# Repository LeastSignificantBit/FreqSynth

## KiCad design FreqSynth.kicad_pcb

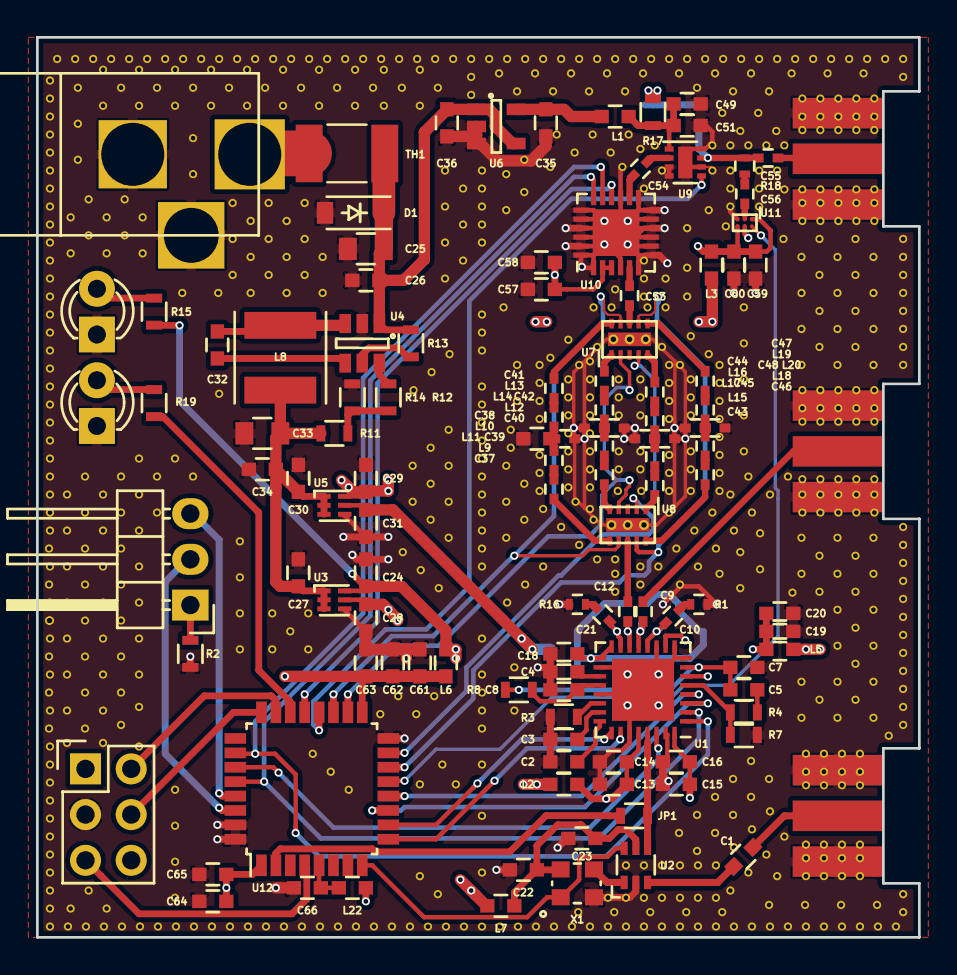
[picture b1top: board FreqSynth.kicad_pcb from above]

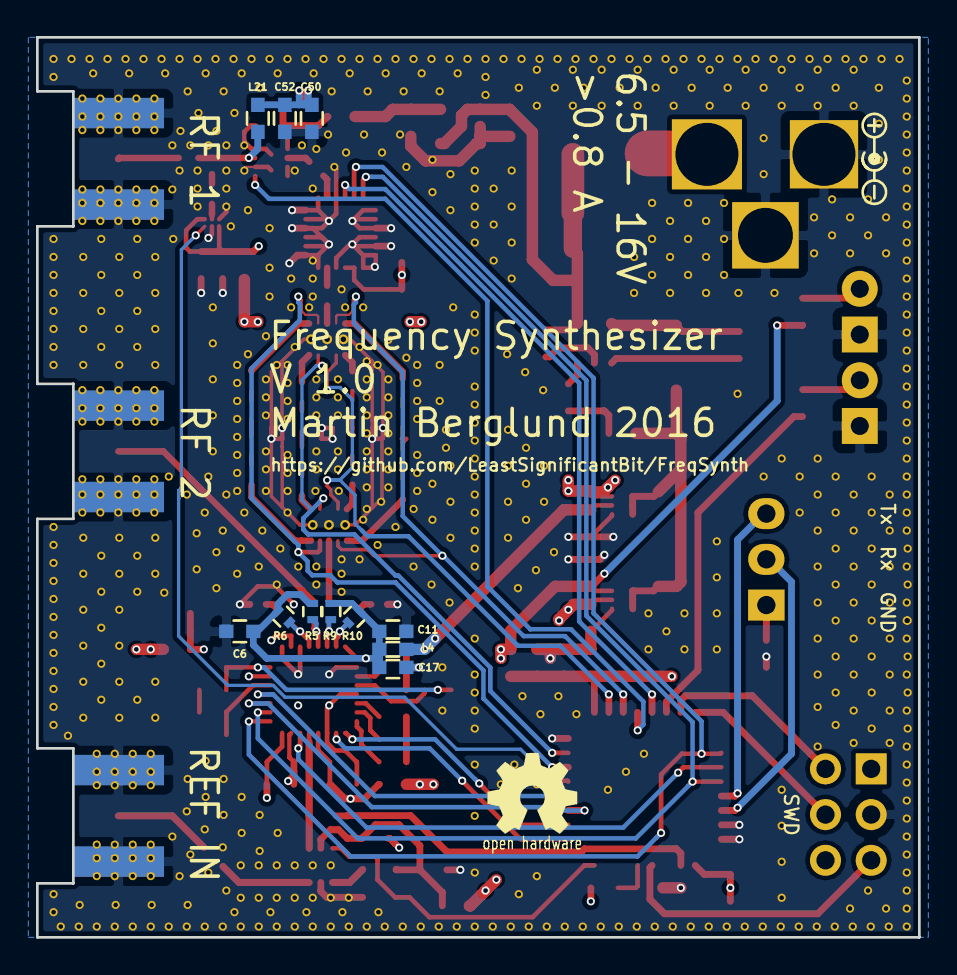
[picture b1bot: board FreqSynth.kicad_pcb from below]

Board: 4 copper layers, 49.0 x 50.0 mm, 131 parts (11 on the bottom side), 96 nets.

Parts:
C1, C6, C11, C13, C15, C17, C19, C22, C50, C57, C59, C62, C64, C66: 10nF; C_0603
C2, C3, C4: 1uF; C_0603
C5, C36, C51: 100nF; C_0603
C7: 12nF; C_0603
C8: 820pF; C_0603
C9, C10, C12, C21, C53, C54, C55, C56: 1nF_RF; C_0402
C14, C16, C18, C20, C23, C58, C60, C63, C65: 100pF; C_0603
C24, C26, C27, C28, C29, C30, C31, C32, C34, C35, C49, C61: 1µF; C_0603
C25, C33: 22µF 16V; C_0805
C37, C38: 100pF_RF; C_0402
C39: 6pF_RF; C_0402
C40, C41: 0.5pF_RF; C_0402
C42: 2pF_RF; C_0402
C43, C44: 0.8pF_RF; C_0402
C45: 4pF_RF; C_0402
C46, C47: 2.4pF_RF; C_0402
C48: 5pF_RF; C_0402
C52: 10pF; C_0603
D1: CPL-DIO-MBR0520; SOD-123
D2: GREEN; LED-3MM
D3: YELLOW; LED-3MM
JP1: Jumper_NC_Small; R_0603
L1, L2, L3, L4, L5, L6, L7, L22: Ferrite; L_0603
L8: 6.8µH 2.5A; NRS5030T6R8MMGJ
L9, L10: 8nH; L_0402
L11: 200nH; L_0603
L12, L13: 2.5nH; L_0402
L14: 0.6nH; L_0402
L15, L16: 5nH; L_0402
L17: 1nH; L_0402
L18, L19: 6.1nH; L_0402
L20: 3nH; L_0402
L21: 100nH; L_0603
P1: CPL-CON-BARREL-2.1MM; BARREL_JACK
P2: RF1; SMA_edge
P3: RF2; SMA_edge
P4: CONN_01X03; Pin_Header_Angled_1x03
P5: REF_IN; SMA_edge
P6: SWD; Pin_Header_Straight_2x03
R1, R5, R6, R9, R10, R16: 49.9R; R_0402
R2: 0R; R_0603
R3: 5.1k; R_0603
R4: 30.1R; R_0603
R7: 90.9R; R_0603
R8: 240R; R_0603
R11: 45.3k; R_0603
R12: 59k; R_0603
R13: 100k; R_0603
R14: 11.3k; R_0603
R15, R19: 180R; R_0603
R17: 1.8R; R_0603
R18: 100R; R_0402
TH1: 750mA working 1.5A trip; SMD_THERMISTOR
U1: MAX2870; QFN-32-1EP_5x5mm_Pitch0.5mm
U2: TS5A3159; SC-70-6
U3, U5: TLV7113333DDSET; WSON-6
U4: AP65101; SOT-23-6
U6: RT9069-50GB; SOT-23-5
U7, U8: SKY13322-375LF; MLPD-10
U9: TRF37A75; DFN-8-1EP_2x2mm_Pitch0.5mm
U10: PE43711; QFN-24-1EP_4x4mm_Pitch0.5mm
U11: LMH2110; WFBGA-6
U12: STM32F030K6T6; LQFP-32_7x7mm_Pitch0.8mm
X1: 25MHz ±5ppm 3.3V 33mA; OSC_2.7x2.4mm

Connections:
/3v3: C29.2, L3.1, L7.1, U5.6
/5V5: C35.1, L1.1, U6.5
/Amplifier/3V3: C57.1, C58.1, C59.1, C60.1, L3.2, U10.2, U10.3, U11.A1, U11.C2
/Amplifier/ATTEN_CS: U10.16, U12.21
/Amplifier/PWDN: U9.5, U12.20
/Amplifier/RF_IN: C53.2, U7.8
/Amplifier/RF_OUT: C55.1, P2.1
/Amplifier/VCC_AMP: C49.2, C51.2, L1.2, R17.1, U9.1
/Clock/3V3: C22.1, C23.1, L7.2, U2.5, X1.4
/Clock/EXT_REF: C1.1, U2.3
/FILT1: U7.9, U8.7, U12.19
/FILT2: U7.7, U8.9, U12.14
/FILT3: U7.4, U8.2, U12.15
/FILT4: U7.2, U8.4, U12.18
/MCU/ADC1: U11.A2, U12.13
/MCU/CE_PLL: U1.4, U12.12
/MCU/CLK_IN: JP1.2, U12.2
/MCU/CS_PLL: U1.3, U12.11
/MCU/EN_PLL: U1.26, U12.9
/MCU/INT_CLK_EN: U2.6, U12.8, X1.1
/MCU/LD_PLL: U1.25, U12.10
/MCU/RX: P4.2, U12.30
/MCU/TX: P4.3, U12.29
/MCU/VCC_D: C61.1, C62.1, C63.1, C64.1, C65.1, L6.2, L22.1, P6.1, U12.1, U12.17
/MISO: U1.30, U12.27
/MOSI: U1.2, U10.18, U12.28
/PLL/CLK_REF: JP1.1, U1.29, U2.4
/PLL/RF+: C12.1, U8.8
/PLL/RF-: C21.1, R16.1
/PLL/RFA_N: C9.2, R5.2, U1.13
/PLL/RFA_P: C10.2, R6.2, U1.12
/PLL/RFB_N: C21.2, R10.2, U1.15
/PLL/RFB_P: C12.2, R9.2, U1.14
/PLL/RF_BALANCED+: C10.1, R1.1
/PLL/RF_BALANCED-: C9.1, P3.1
/PLL/TUNE: C8.2, R8.1, U1.20
/PLL/VCC_D: C13.1, C14.1, C15.1, C16.1, L2.2, U1.28, U1.32
/PLL/VCC_PLL: C19.1, C20.1, L5.2, U1.6, U1.10
/PLL/VCC_RF: C6.1, C11.1, C17.1, C18.1, L4.2, R5.1, R6.1, R9.1, R10.1, U1.16, U1.17
/Power/4V0: C27.1, C30.1, C33.1, C34.1, L8.2, R11.2, U3.1, U3.2, U3.3, U5.1, U5.2, U5.3
/Power/VCC_D: C24.2, L2.1, L6.1, R15.1, U3.6
/Power/VCC_PLL: C28.1, L5.1, U3.5
/Power/VCC_RF: C31.1, L4.1, U5.5
/Power/VIN: C25.1, C26.1, C36.1, D1.1, R13.1, TH1.1, U4.1, U6.1, U6.4
/SCK: U1.1, U10.17, U12.26
Earth: C2.1, C3.1, C4.1, C6.2, C7.1, C8.1, C11.2, C13.2, C14.2, C15.2, C16.2, C17.2, C18.2, C19.2, C20.2, C22.2, C23.2, C24.1, C25.2, C26.2, C27.2, C28.2, C29.1, C30.2, C31.2, C33.2, C34.2, C35.2, C36.2, C39.2, C42.2, C45.2, C48.2, C49.1, C50.2, C51.1, C52.1, C57.2, C58.2, C59.2, C60.2, C61.2, C62.2, C63.2, C64.2, C65.2, C66.2, D1.2, D2.1, D3.1, L11.2, L14.2, L17.2, L20.2, P1.2, P1.3, P2.2, P3.2, P5.2, P6.3, R1.2, R2.2, R3.1, R7.1, R14.1, R16.2, U1.8, U1.9, U1.11, U1.18, U1.21, U1.27, U1.31, U1.33, U2.2, U3.4, U4.2, U5.4, U6.2, U6.3, U7.11, U8.11, U9.3, U9.4, U9.6, U9.8, U9.9, U10.1, U10.4, U10.6, U10.7, U10.8, U10.9, U10.10, U10.11, U10.12, U10.13, U10.15, U10.19, U10.20, U10.21, U10.22, U10.23, U10.24, U10.25, U11.B2, U11.C1, U12.16, U12.31, U12.32, X1.2
unnamed: C1.2, P5.1
unnamed: C2.2, U1.24
unnamed: C3.2, U1.23
unnamed: C4.2, U1.19
unnamed: C5.1, C7.2, R8.2, U1.7
unnamed: C5.2, R4.1
unnamed: C32.1, U4.4
unnamed: C32.2, L8.1, U4.3
unnamed: C37.1, U8.6
unnamed: C37.2, L9.2
unnamed: C38.1, L10.2
unnamed: C38.2, U7.10
unnamed: C39.1, L9.1, L10.1, L11.1
unnamed: C40.1, U8.5
unnamed: C40.2, L12.2
unnamed: C41.1, U7.1
unnamed: C41.2, L13.2
unnamed: C42.1, L12.1, L13.1, L14.1
unnamed: C43.1, U8.1
unnamed: C43.2, L15.2
unnamed: C44.1, U7.5
unnamed: C44.2, L16.2
unnamed: C45.1, L15.1, L16.1, L17.1
unnamed: C46.1, U8.10
unnamed: C46.2, L18.2
unnamed: C47.1, U7.6
unnamed: C47.2, L19.2
unnamed: C48.1, L18.1, L19.1, L20.1
unnamed: C50.1, C52.2, L21.1, R17.2
unnamed: C53.1, U10.5
unnamed: C54.1, U9.2
unnamed: C54.2, U10.14
unnamed: C55.2, L21.2, R18.1, U9.7
unnamed: C56.1, U11.B1
unnamed: C56.2, R18.2
unnamed: C66.1, L22.2, U12.5
unnamed: D2.2, R15.2
unnamed: D3.2, R19.2
unnamed: P1.1, TH1.2
unnamed: P4.1, R2.1
unnamed: P6.2, U12.23
unnamed: P6.4, U12.24
unnamed: P6.5, U12.4
unnamed: R3.2, U1.22
unnamed: R4.2, R7.2, U1.5
unnamed: R11.1, R12.1, R14.2
unnamed: R12.2, U4.6
unnamed: R13.2, U4.5
unnamed: R19.1, U12.22
unnamed: U2.1, X1.3

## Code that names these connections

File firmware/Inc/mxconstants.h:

/**
  ******************************************************************************
  * File Name          : mxconstants.h
  * Description        : This file contains the common defines of the application
  ******************************************************************************
  *
  * COPYRIGHT(c) 2016 STMicroelectronics
  *
  * Redistribution and use in source and binary forms, with or without modification,
  * are permitted provided that the following conditions are met:
  *   1. Redistributions of source code must retain the above copyright notice,
  *      this list of conditions and the following disclaimer.
  *   2. Redistributions in binary form must reproduce the above copyright notice,
  *      this list of conditions and the following disclaimer in the documentation
  *      and/or other materials provided with the distribution.
  *   3. Neither the name of STMicroelectronics nor the names of its contributors
  *      may be used to endorse or promote products derived from this software
  *      without specific prior written permission.
  *
  * THIS SOFTWARE IS PROVIDED BY THE COPYRIGHT HOLDERS AND CONTRIBUTORS "AS IS"
  * AND ANY EXPRESS OR IMPLIED WARRANTIES, INCLUDING, BUT NOT LIMITED TO, THE
  * IMPLIED WARRANTIES OF MERCHANTABILITY AND FITNESS FOR A PARTICULAR PURPOSE ARE
  * DISCLAIMED. IN NO EVENT SHALL THE COPYRIGHT HOLDER OR CONTRIBUTORS BE LIABLE
  * FOR ANY DIRECT, INDIRECT, INCIDENTAL, SPECIAL, EXEMPLARY, OR CONSEQUENTIAL
  * DAMAGES (INCLUDING, BUT NOT LIMITED TO, PROCUREMENT OF SUBSTITUTE GOODS OR
  * SERVICES; LOSS OF USE, DATA, OR PROFITS; OR BUSINESS INTERRUPTION) HOWEVER
  * CAUSED AND ON ANY THEORY OF LIABILITY, WHETHER IN CONTRACT, STRICT LIABILITY,
  * OR TORT (INCLUDING NEGLIGENCE OR OTHERWISE) ARISING IN ANY WAY OUT OF THE USE
  * OF THIS SOFTWARE, EVEN IF ADVISED OF THE POSSIBILITY OF SUCH DAMAGE.
  *
  ******************************************************************************
  */
/* Define to prevent recursive inclusion -------------------------------------*/
#ifndef __MXCONSTANT_H
#define __MXCONSTANT_H
  /* Includes ------------------------------------------------------------------*/

/* USER CODE BEGIN Includes */

/* USER CODE END Includes */

/* Private define ------------------------------------------------------------*/

#define INT_CLK_EN_Pin GPIO_PIN_2
#define INT_CLK_EN_GPIO_Port GPIOA
#define EN_PLL_Pin GPIO_PIN_3
#define EN_PLL_GPIO_Port GPIOA
#define LD_PLL_Pin GPIO_PIN_4
#define LD_PLL_GPIO_Port GPIOA
#define CS_PLL_Pin GPIO_PIN_5
#define CS_PLL_GPIO_Port GPIOA
#define CE_PLL_Pin GPIO_PIN_6
#define CE_PLL_GPIO_Port GPIOA
#define ADC_POWER_DET_Pin GPIO_PIN_7
#define ADC_POWER_DET_GPIO_Port GPIOA
#define FILT2_Pin GPIO_PIN_0
#define FILT2_GPIO_Port GPIOB
#define FILT3_Pin GPIO_PIN_1
#define FILT3_GPIO_Port GPIOB
#define FILT4_Pin GPIO_PIN_8
#define FILT4_GPIO_Port GPIOA
#define FILT1_Pin GPIO_PIN_9
#define FILT1_GPIO_Port GPIOA
#define PWDWN_Pin GPIO_PIN_10
#define PWDWN_GPIO_Port GPIOA
#define ATTEN_CS_Pin GPIO_PIN_11
#define ATTEN_CS_GPIO_Port GPIOA
#define RED_LED_Pin GPIO_PIN_12
#define RED_LED_GPIO_Port GPIOA
/* USER CODE BEGIN Private defines */

/* USER CODE END Private defines */

/**
  * @}
  */ 

/**
  * @}
*/ 

#endif /* __MXCONSTANT_H */
/************************ (C) COPYRIGHT STMicroelectronics *****END OF FILE****/

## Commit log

2016-08-29 init
2016-08-29 fixed broken stuff
2016-08-30 multiple additions
2016-08-30 Amplifier
2016-08-30 added amplifier
2016-08-31 Set the designrules to match 4 layer OSHpark DRC
2016-08-31 Fixed Amplifier, Added manf# field, ERC cleanup
2016-08-31 housekeeping
2016-08-31 attenuator
2016-09-01 Removed rescuelib
2016-09-01 Added some inductor values
2016-09-01 small edit
2016-09-02 added library parts
2016-09-02 Added manf# to most of the parts
2016-09-02 Started on the board even though theres some components missing
2016-09-02 Added a todolist and solved som small crap
2016-09-03 Outline starts to come togeter
2016-09-03 Fixed USB mini B
2016-09-03 Added power meter, swaped some pins, and routetd most of the RF
2016-09-04 Starting to clean up
2016-09-05 Board layout almost done
2016-09-05 Board layout done, no ERC or DRC:s left
2016-09-10 Major rework
    Removed star ground.
    Switched MCU.
    Smaller board outline - Ripped up almost the entire ratsnest.
    Eliminated one crystal.
    No more USB
    New debug header
2016-09-10 Finished routing the preliminary layout
2016-09-11 Added new leds and switched swd header to 0.1" instead of jst
2016-09-11 Added some missing part numbers
2016-09-12 fixed the barreljack
2016-09-12 All ICS duble-checked! some RF solved
2016-09-13 reroutet the entire board
2016-09-13 Almost finished, Via stitching in place plus decals
2016-09-13 RC2
    Fixed oval holes that are not allowed and set the solder mask parameters to the limit
2016-09-24 RC3 - fixed soldermask
2016-09-30 Added a skeleton for the firmware development.\n\nIt only just compiles, with an example usart port
2016-10-01 Fixed a Command interface for the firmware
    Added a small test routine to main to demonstrate/test
2016-10-13 stuff
2016-10-15 Switched library to the default output from STM32Cube
2016-10-15 Compiled and tested!
2016-10-16 Forgot some files...
2016-10-18 Added a skeleton for most classes
2016-10-18 Added a tiny printf to help with printing
2016-10-20 Added proper Licence + some minor tweaks
2016-10-20 Fleshed out the MAX2870 class and set the overall structure of the program.
2016-10-27 step
2017-01-22 start to check for errors
2017-01-23 some dubugging later..
